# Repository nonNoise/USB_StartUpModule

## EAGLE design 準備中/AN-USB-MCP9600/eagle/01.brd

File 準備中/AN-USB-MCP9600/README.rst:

========================================================================
ＵＳＢで始めるＫ型熱電対計測モジュール
========================================================================

作成日:

.. image:: ./img/resize/AN-USB-S11059.jpg
    :width: 480px

■ 概要
------------------------------------------------------------------------

■ 回路図
------------------------------------------------------------------------

.. image:: ./img/AN-USB-MCP9600.PNG
    :width: 480px

■ 部品表
------------------------------------------------------------------------

■ サンプルプログラム
------------------------------------------------------------------------

    pip install PyMCP2221A

■ 参考資料
------------------------------------------------------------------------

::
    
    MIT License
    Copyright (c) 2018 ArtifactNoise,LLP/Yuta Kitagami

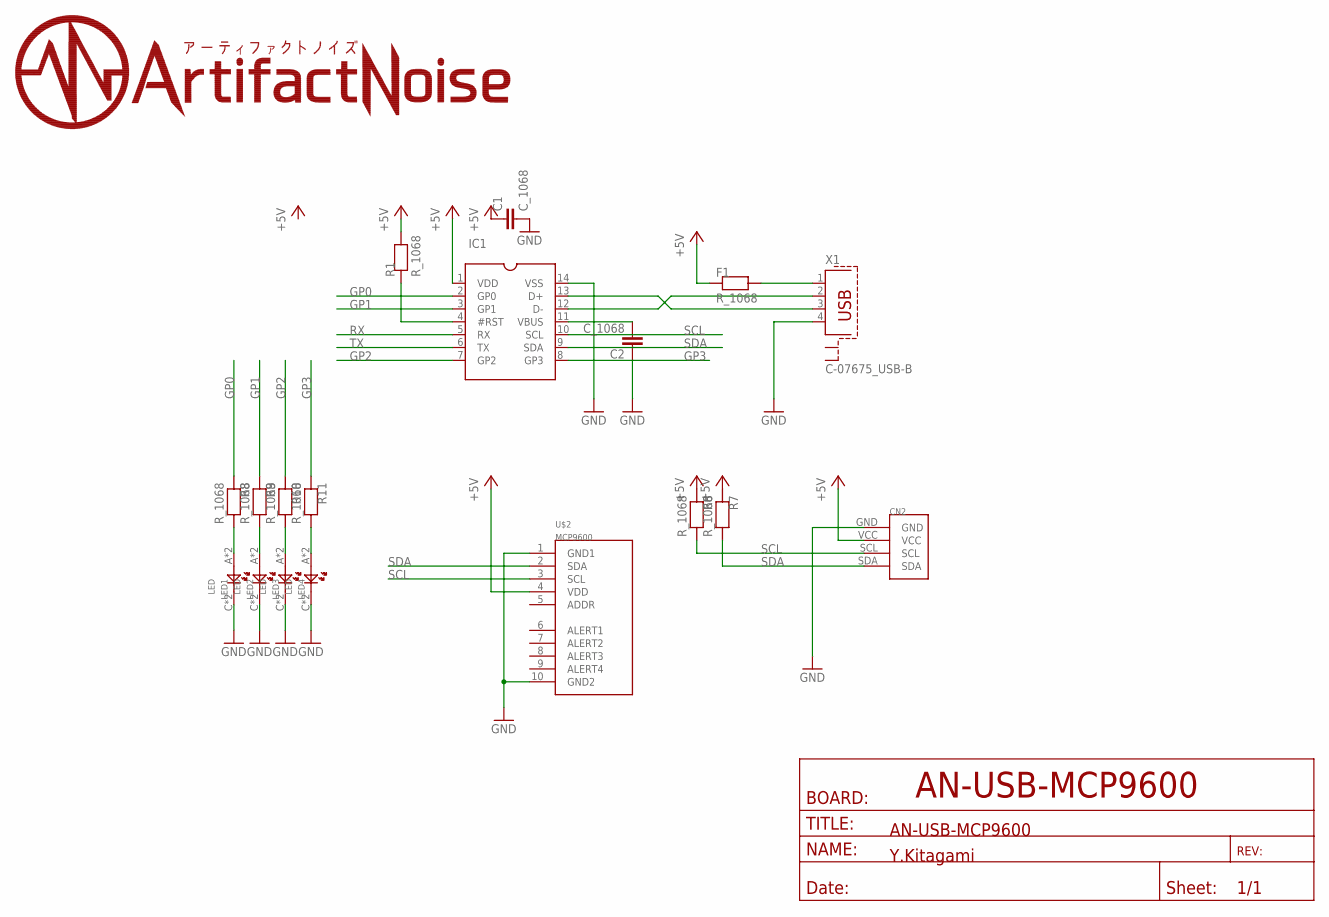
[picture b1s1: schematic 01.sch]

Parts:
C1, C2: C_1068; C0603
CN2: PIN4
F1: R_1068; R0603
IC1: _MCP2221A-I/PS; SOCKET-14
LED1, LED2, LED3, LED4: LED; CHIPLED_0805
R1, R6, R7, R8, R9, R10, R11: R_1068; R0603
U$2: MCP9600
X1: C-07675_USB-B; PN61729-S

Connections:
+5V: C1.1, C1.D1 (1), CN2.VCC, F1.1, F1.D1 (1), IC1.1 (VDD), R1.2, R1.D2 (2), R6.1, R6.D1 (1), R7.1, R7.D1 (1), U$2.4 (VDD)
GND: C1.2, C1.D2 (2), C2.1, C2.D1 (1), CN2.GND, IC1.14 (VSS), LED1.C, LED1.DC (C), LED2.C, LED2.DC (C), LED3.C, LED3.DC (C), LED4.C, LED4.DC (C), U$2.1 (GND1), U$2.10 (GND2), X1.4
GP0: IC1.2 (GP0), R8.1, R8.D1 (1)
GP1: IC1.3 (GP1), R9.1, R9.D1 (1)
GP2: IC1.7 (GP2), R10.1, R10.D1 (1)
GP3: IC1.8 (GP3), R11.1, R11.D1 (1)
unnamed: IC1.4 (#RST), R1.1, R1.D1 (1)
unnamed: IC1.13 (D+), X1.3
unnamed: IC1.12 (D-), X1.2
unnamed: C2.2, C2.D2 (2), IC1.11 (VBUS)
unnamed: F1.2, F1.D2 (2), X1.1
unnamed: LED1.A, LED1.DA (A), R8.2, R8.D2 (2)
unnamed: LED2.A, LED2.DA (A), R9.2, R9.D2 (2)
unnamed: LED3.A, LED3.DA (A), R10.2, R10.D2 (2)
unnamed: LED4.A, LED4.DA (A), R11.2, R11.D2 (2)
RX: IC1.5 (RX)
SCL: CN2.SCL, IC1.10 (SCL), R6.2, R6.D2 (2), U$2.3 (SCL)
SDA: CN2.SDA, IC1.9 (SDA), R7.2, R7.D2 (2), U$2.2 (SDA)
TX: IC1.6 (TX)

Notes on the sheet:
AN-USB-MCP9600
Y.Kitagami

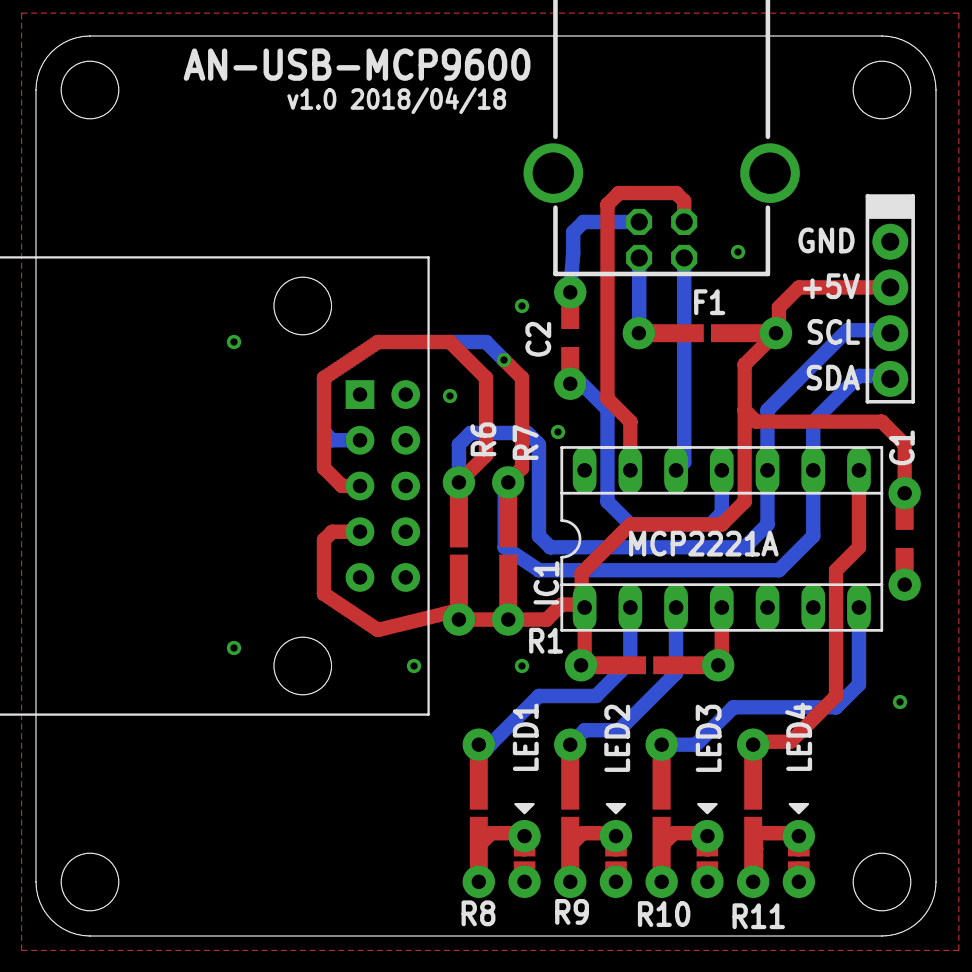
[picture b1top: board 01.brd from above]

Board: 2 copper layers, 50.0 x 50.0 mm, 19 parts (1 on the bottom side), 17 nets.

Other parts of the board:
U$1: AN-LOGO2

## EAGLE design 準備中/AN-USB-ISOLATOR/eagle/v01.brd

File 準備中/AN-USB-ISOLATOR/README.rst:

========================================================================
USBで始める際のPC保護用絶縁アダプター
========================================================================

作成日:

.. image:: ./img/resize/AN-USB-S11059.jpg
    :width: 480px

■ 概要
------------------------------------------------------------------------

■ 回路図
------------------------------------------------------------------------

.. image:: ./img/S11059.PNG
    :width: 480px

■ 部品表
------------------------------------------------------------------------

■ 参考資料
------------------------------------------------------------------------

::
    
    MIT License
    Copyright (c) 2018 ArtifactNoise,LLP/Yuta Kitagami

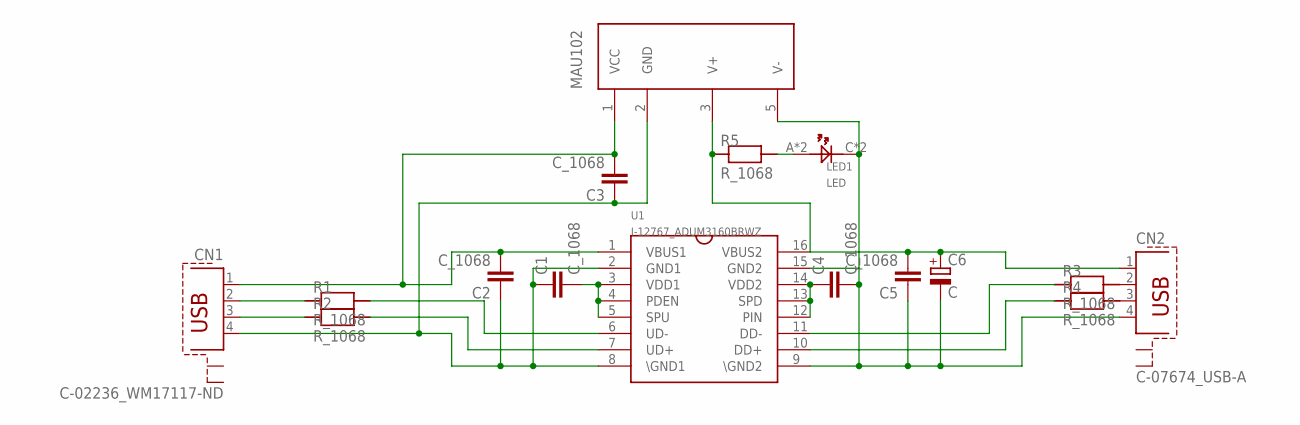
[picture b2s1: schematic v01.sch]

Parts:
C1, C2, C3, C4, C5: C_1068; C0603
C6: C; 153CLV-1012
CN1: C-02236_WM17117-ND; WM17117-ND
CN2: C-07674_USB-A; PN87520-S
LED1: LED; CHIPLED_0805
MAU102: M-04131_MAU102; MAU102
R1, R2, R3, R4, R5: R_1068; R0603
U1: I-12767_ADUM3160BRWZ; ADUM3160BRWZ

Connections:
GNDA: C1.1, C1.D1 (1), C2.1, C2.D1 (1), C3.1, C3.D1 (1), CN1.4, MAU102.2 (GND), U1.2 (GND1), U1.8 (\GND1)
GNDB: C4.2, C4.D2 (2), C5.1, C5.D1 (1), C6.-, C6.-1 (-), C6.-2 (-), CN2.4, LED1.C, LED1.DC (C), MAU102.5 (V-), U1.9 (\GND2), U1.15 (GND2)
unnamed: C1.2, C1.D2 (2), U1.3 (VDD1), U1.4 (PDEN), U1.5 (SPU)
unnamed: R1.2, R1.D2 (2), U1.6 (UD-)
unnamed: R2.2, R2.D2 (2), U1.7 (UD+)
unnamed: CN1.2, R1.1, R1.D1 (1)
unnamed: CN1.3, R2.1, R2.D1 (1)
unnamed: C4.1, C4.D1 (1), U1.12 (PIN), U1.13 (SPD), U1.14 (VDD2)
unnamed: CN2.2, R3.2, R3.D2 (2)
unnamed: CN2.3, R4.2, R4.D2 (2)
unnamed: LED1.A, LED1.DA (A), R5.2, R5.D2 (2)
unnamed: R3.1, R3.D1 (1), U1.11 (DD-)
unnamed: R4.1, R4.D1 (1), U1.10 (DD+)
VCCA: C2.2, C2.D2 (2), C3.2, C3.D2 (2), CN1.1, MAU102.1 (VCC), U1.1 (VBUS1)
VCCB: C5.2, C5.D2 (2), C6.+, C6.+1 (+), C6.+2 (+), CN2.1, MAU102.3 (V+), R5.1, R5.D1 (1), U1.16 (VBUS2)

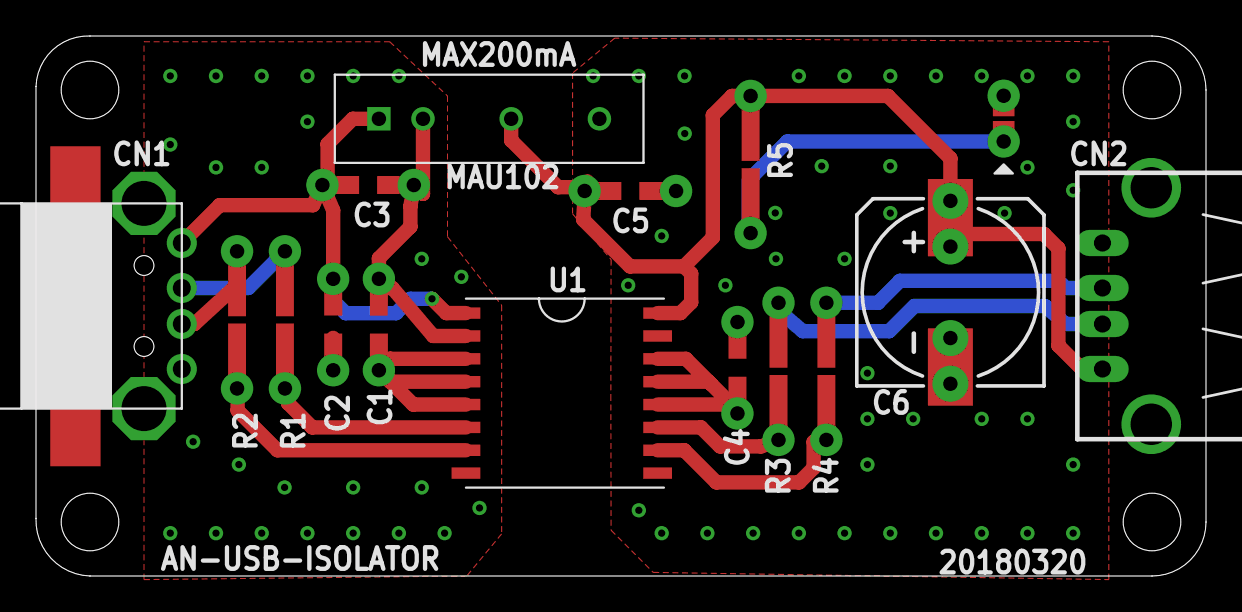
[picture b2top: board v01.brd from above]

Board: 2 copper layers, 65.0 x 30.0 mm, 17 parts (1 on the bottom side), 15 nets.

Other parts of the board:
U$2: AN-LOGO2

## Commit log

2018-04-05 draft
2018-04-22 技術書典４記念
2018-04-24 一部修正
2018-04-24 Pythonについて追加
2018-04-30 Q&A追加
2018-04-30 サンプルソース追加
2018-04-30 APIを少し修正
2018-05-01 ドキュメント更新
2018-05-06 サンプル追加
2018-05-08 準備中更新
2018-05-08 .gitignore
